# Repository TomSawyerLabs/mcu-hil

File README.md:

# mcu-hil

Hardware-in-the-loop boards for testing software against real microcontrollers.
A Raspberry Pi (Compute Module or standard Pi) powers, programs, clocks, resets and talks to
the microcontroller(s) on the board, so tests run against real silicon in a repeatable way.

AVRs come first (starting with the ATmega16U2 from v1). Other families (XMEGA, AVR32 UC3, and
more later) get their own boards built from the same base design.

## Variants

Each variant is a complete board with its MCU(s) on it. They share schematic sheets and one GPIO map.

- **CM4/CM5 carrier** (primary): same 55 × 40 mm outline as the Compute Module, so they stack.
  USB-C for power and rpiboot, Ethernet for network boot, microSD.
- **Pi HAT**: for 40-pin Raspberry Pi boards. Powered by the Pi; its USB-C is a data link back to
  the Pi through a short loopback cable.

Designed in KiCad. Every part has an LCSC part number and is chosen to be in stock, so boards can be
ordered fully assembled from JLCPCB.

## Status

v2 is being designed. See [plans/v2-design.md](plans/v2-design.md), the
[v1 design review](docs/v1-review.md), the [v2 requirements draft](docs/v2-requirements.md),
the [v2 pin map](docs/v2-pinmap.md), the [parts list](docs/v2-parts.md) and the
[schematic notes](docs/v2-schematic.md).

The KiCad 10 projects are in `hw/carrier/` and `hw/hat/`. Their schematics are generated from
[`tools/schgen/design.py`](tools/schgen/design.py) (`cd tools && python -m schgen`).

## v1 (AVR Test HAT)

This repo was `avr-test-hat`. The v1 design was an Altium project for a single Pi HAT with an
on-board ATmega16U2. Its files are no longer on `master` but are kept in history:

- Tag [`v1`](https://github.com/TomSawyerLabs/mcu-hil/tree/v1) (also branch
  [`v1-archive`](https://github.com/TomSawyerLabs/mcu-hil/tree/v1-archive)): the Altium project as it was.
- v1's simplified block diagram: [docs/v1-images/Circuits.drawio.svg](docs/v1-images/Circuits.drawio.svg).

v1 credits: [Raspberry Pi HAT Template](https://workspace.circuitmaker.com/Projects/Details/jonaslorander/Raspberry-Pi-HAT-Template)
by [Jonas Lorander](https://workspace.circuitmaker.com/User/Details/jonaslorander), and [SnapEDA](https://www.snapeda.com).

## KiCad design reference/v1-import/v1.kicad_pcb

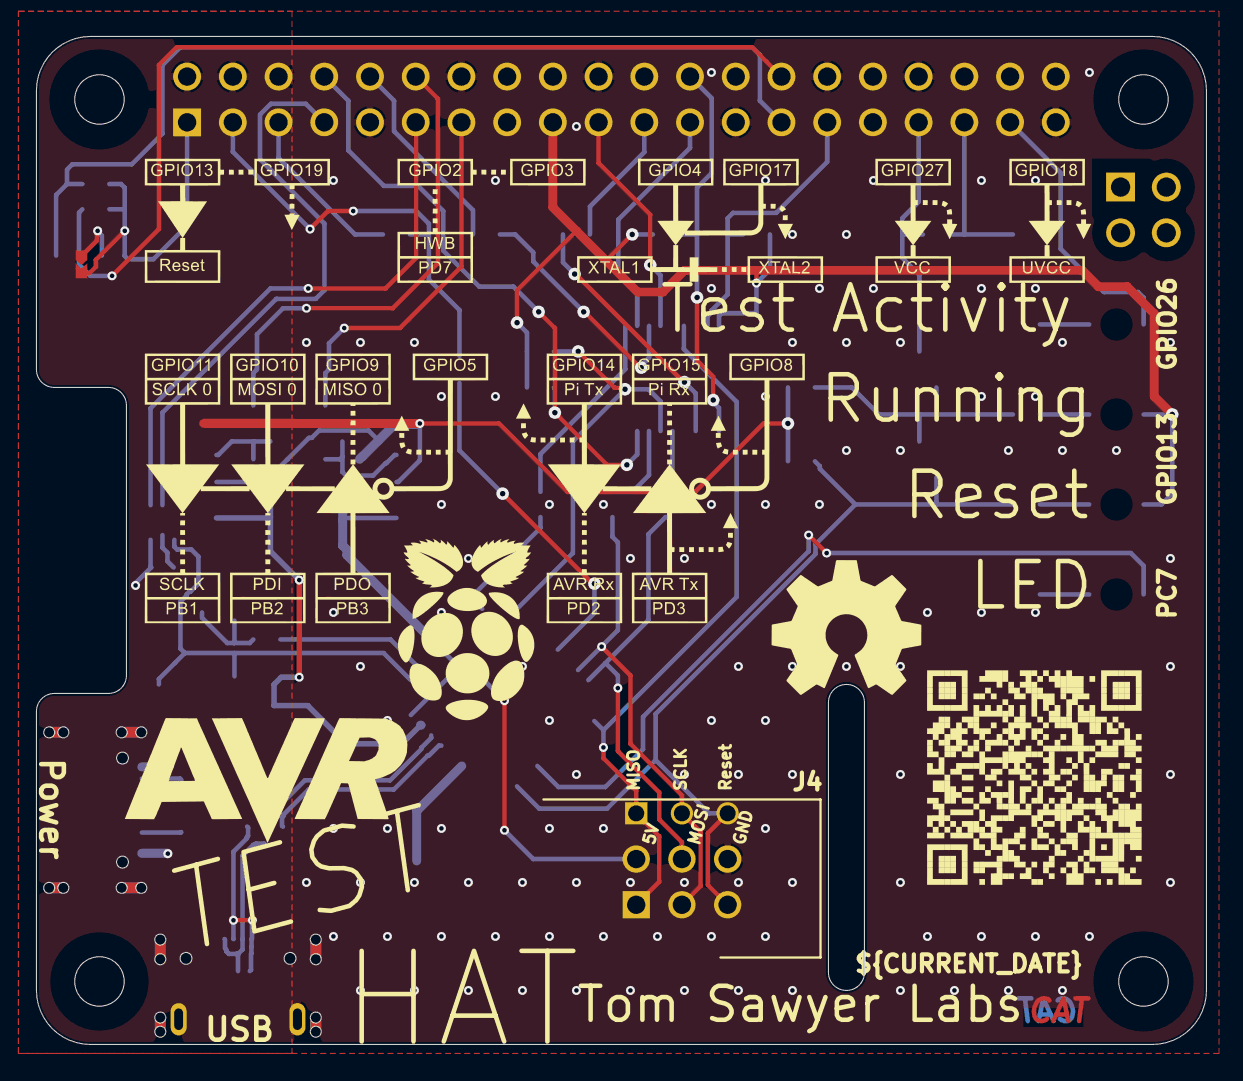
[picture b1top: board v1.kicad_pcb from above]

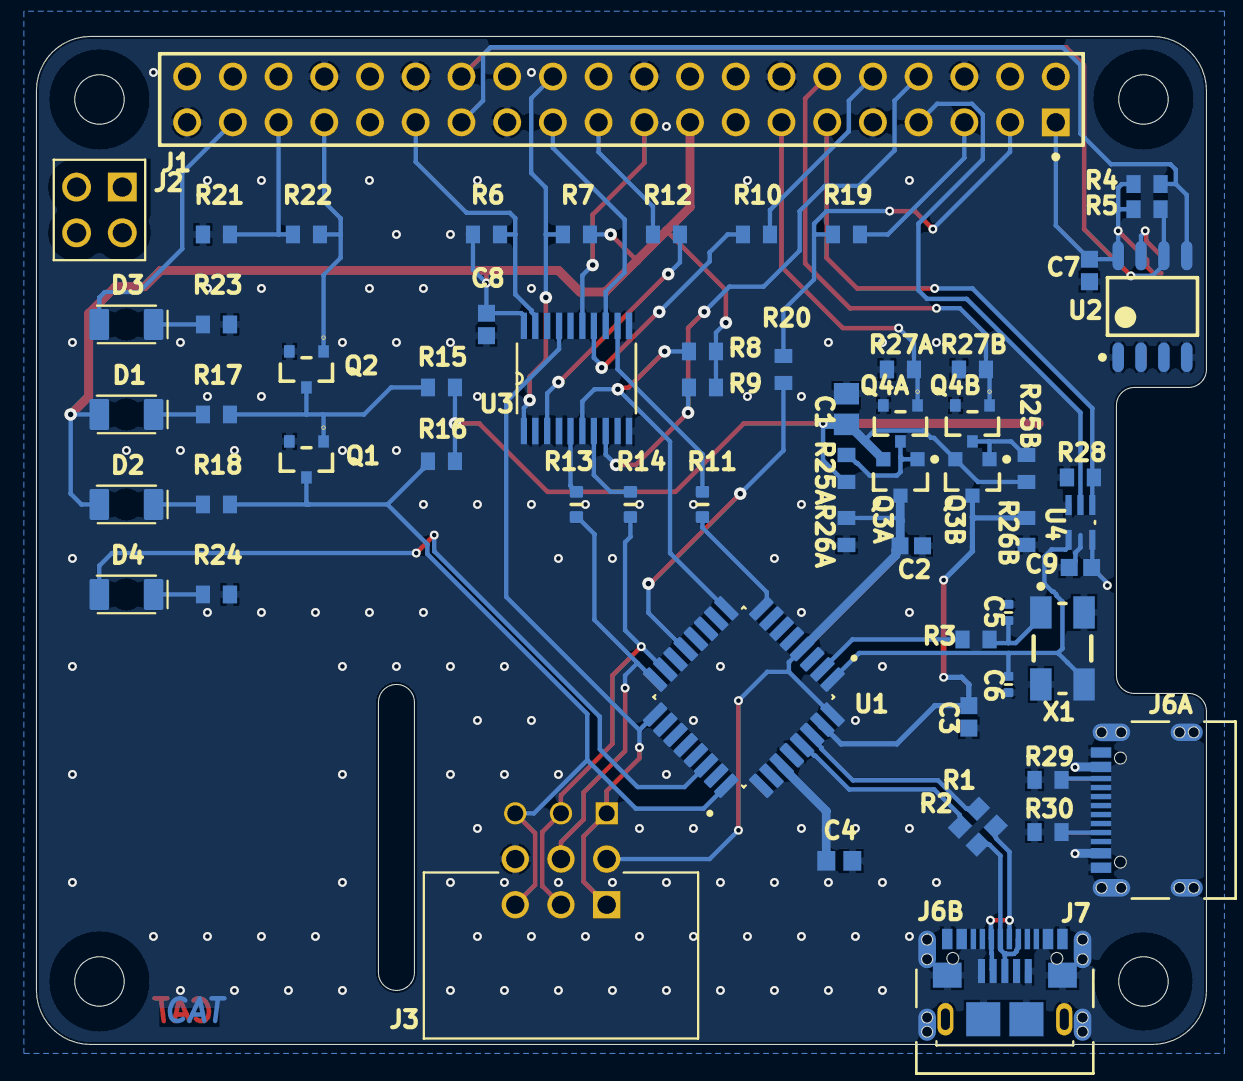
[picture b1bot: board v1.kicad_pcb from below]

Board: 2 copper layers, 65.0 x 56.0 mm, 65 parts (63 on the bottom side), 57 nets.

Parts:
C1: Capacitor 10 uF +/- 10% 16 V 0805; CAPC2013X135X45NL10T25
C2, C3, C7, C8, C9: Capacitor 100 nF +/-10% 50 V 0603; CAPC1608X90X40NL10T20
C4: Capacitor 1uF +/- 10% 16V 0603; CAPC1608X90X35ML15T15
C5, C6: Capacitor 12pF +/-10% 50V 0402; CAPC0402(1005)33_L
D1, D2, D3, D4: LTST-C230KFKT; LEDC3216X110
J1: Harwin M20-7832046; PCB-677180-1
J2: PPPC022LFBN-RC; SULLINS_PPPC022LFBN-RC
J3: 2-1761605-1; TE_2-1761605-1
J4: 30306-6002HB; 3M_30306-6002HB
J5: JUMPER
J6A, J6B: USB4105-GF-A; USB4105_GCT
J7: 10118193-0001LF; AMPHENOL_10118193-0001LF
Q1, Q2, Q4A, Q4B: 2N7002,215; NXP-SOT23-3_V
Q3A, Q3B: CJ2305; JSCJ-SOT23-3_V
R1, R2: Resistor 22R +/-1% 0603 100 mW; RESC1609X50X30ML08T20
R3, R4, R5, R6, R7, R8, R9, R10, R12, R15, R16, R17, R18, R19, R20, R21, R22, R23, R24, R25A, R25B, R26A, R26B, R27A, R27B, R28, R29, R30: Resistor 1k +/-1% 0603 100 mW; RESC1608X55X25ML10T15
R11, R13, R14: Resistor 120R +/-5 % 0603 0.1 W; RESC0603(1608)_L
U1: ATMEGA16U2-AU; QFP80P900X900X120-32N
U2: CAT24C32WI-GT3; ONSC-SOIC-8-751BD-01_M
U3: 74LVC244APW,118; SOP65P640X110-20N
U4: 74AHCT1G126SE-7; SOT65P210X110-5N
X1: ABM3B-16.000MHZ-B2-T; ABRA-ABM3B-4_V

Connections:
3V3: C7.2, C8.2, D1.A, D2.A, J1.1, J1.17, J5.2, R4.2, R5.2, R6.2, R7.2, R8.2, R9.2, U2.8, U3.20
5V: C1.1, C9.2, J1.2, J1.4, J6A.A4-B9, J6A.B4-A9, Q3A.2, Q3B.2, R15.2, R16.2, R25A.2, R25B.2, U4.5
AVR Activity: D4.A, U1.22
AVR Clock: C6.2, U1.1, U4.4, X1.3
AVR Rx: R11.2, U1.8
AVR Tx: R8.1, U1.9, U3.6
AVR USB Enable: J1.12, Q4B.1, R27B.2
AVR VCC Enable: J1.13, Q4A.1, R27A.2
A_N: R1.2, U1.30
A_P: R2.2, U1.29
Clock Override: J1.7, U4.2
Clock Override Enable: J1.11, R28.2, U4.1
DA_N: J6A.A7, J6A.B7
DA_P: J6A.A6, J6A.B6
DB_N: J6B.A7, J6B.B7, J7.2, R1.1
DB_P: J6B.A6, J6B.B6, J7.3, R2.1
Device_MISO: J3.1, J4.1, U1.17, U3.17
Device_MOSI: J3.4, J4.4, R13.2, U1.16
Device_SCLK: J3.3, J4.3, R14.2, U1.15
GND: C1.2, C2.1, C3.1, C4.2, C5.1, C6.1, C7.1, C8.1, C9.1, J1.6, J1.9, J1.14, J1.20, J1.25, J1.30, J1.34, J1.39, J3.6, J4.6, J6A.A1-B12, J6A.B1-A12, J6B.A1-B12, J6B.B1-A12, J7.5, J7.S1, J7.S2, J7.S3, J7.S4, J7.S5, J7.S6, Q1.2, Q2.2, Q4A.2, Q4B.2, R21.1, R23.1, R24.1, R26A.1, R26B.1, R27A.1, R27B.1, R28.1, R29.1, R30.1, U1.3, U1.28, U2.1, U2.2, U2.3, U2.4, U3.2, U3.4, U3.10, U3.11, U4.3, X1.2, X1.4
GPIO2: J1.3, R19.1, R20.2
GPIO3: J1.5, R19.2
GPIO5: J1.29, R6.1, U3.19
GPIO8: J1.24, R7.1, U3.1
GPIO9: J1.21, R12.1
GPIO10: J1.19, U3.15
GPIO11: J1.23, U3.13
GPIO13: J1.33, Q2.1, R22.1
GPIO14: J1.8, R9.1, U3.8
GPIO15: J1.10, R10.1
GPIO19: J1.35, R21.2, R22.2
GPIO26: D3.A, J1.37
HWB: R20.1, U1.13
ID_SC: J1.28, R5.1, U2.6
ID_SD: J1.27, R4.1, U2.5
NetC4_1: C4.1, U1.27
NetC5_2: C5.2, R3.1, X1.1
NetD1_C: D1.C, R17.2
NetD2_C: D2.C, R18.2
NetD3_C: D3.C, R23.2
NetD4_C: D4.C, R24.2
NetJ5_1: J5.1, U2.7
NetJ6A_A5: J6A.A5, R30.2
NetJ6A_B5: J6A.B5, R29.2
NetJ6B_A4-B9: J6B.A4-B9, J6B.B4-A9
NetQ1_1: Q1.1, Q2.3, R15.1, R17.1
NetQ3A_1: Q3A.1, Q4A.3, R25A.1
NetQ3B_1: Q3B.1, Q4B.3, R25B.1
NetR3_2: R3.2, U1.2
NetR10_2: R10.2, U3.14
NetR11_1: R11.1, U3.12
NetR12_2: R12.2, U3.3
NetR13_1: R13.1, U3.5
NetR14_1: R14.1, U3.7
Reset: J3.5, J4.5, Q1.3, R16.1, R18.1, U1.24
UVCC: C3.2, Q3B.3, R26B.2, U1.31
VCC: C2.2, J3.2, J4.2, Q3A.3, R26A.2, U1.4, U1.32

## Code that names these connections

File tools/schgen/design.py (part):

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    R(sh, "100k", "RST_GATE", "DUT_5V")
    NMOS(sh, "RST_GATE", "RESET_RELEASE")
    R(sh, "100k", "RESET_RELEASE", "GND")
    # HWB (PD7) assert.
    NMOS(sh, "DUT_PD7", "HWB_ASSERT")
    R(sh, "100k", "HWB_ASSERT", "GND")
    return sh
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def sheet_hv() -> Sheet:
    sh = Sheet("hv", "High-voltage programming (option HV)")
    sh.notes = [
        "12 V boost (MT3608, GPIO26) and a switch that puts it on RESET (GPIO25). Both default off.",
        "FB divider 100k/5.1k: 12.36 V nominal. The 1k series resistor drops about 0.25 V at the 250 uA RESET current,",
        "so RESET sees 11.9-12.4 V (spec 11.5-12.5 V).",
        "TCA6416A: VCCP on +5V (always up before +3V3, as TI recommends). ~RESET is pulled up to DUT_5V, so the",
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
# ------------------------------------------------------------------------------------------- carrier
CM_GPIO = {
    "GPIO2": "I2C_SDA", "GPIO3": "I2C_SCL", "GPIO4": "GPCLK0", "GPIO9": "ISP_MISO", "GPIO10": "ISP_MOSI",
    "GPIO11": "ISP_SCK", "GPIO12": "RESET_RELEASE", "GPIO13": "HWB_ASSERT", "GPIO14": "PI_TXD",
    "GPIO15": "PI_RXD", "GPIO16": "ISP_OE", "GPIO17": "UART_OE", "GPIO18": "CLK_OE", "GPIO19": "PWR_ALERT",
    "GPIO20": "USB_S0", "GPIO21": "USB_S1", "GPIO22": "DUT_PWR_EN", "GPIO24": "STATUS_LED",
    "GPIO25": "HV_APPLY", "GPIO26": "HV_BOOST_EN", "GPIO27": "SI_CLK_OE",
}


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    sh = Sheet("cm", "Compute Module 4/5 connectors", paper="A2")
    sh.notes = [
        "Hirose DF40C-100DS-0.4V(51), 1.5 mm stack. CM4 and CM5 share every pin used here.",
        "GPIO_VREF to +3V3 (3.3 V GPIO). ID_SD/ID_SC, GLOBAL_EN/PMIC_EN, EEPROM_nWP and the 1.8 V outputs are unused.",
        "CM5's USB-C CC pins (94/96) are left open: the carrier's own 5.1k Rd works for both CM4 and CM5",
        "(CM5 then runs without 5 A PD negotiation).",
    ]
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        "HAT+ rules: ID_SD/ID_SC carry only the EEPROM and 3.9k pull-ups to 3.3 V. EEPROM WP has a 1k pull-up;",
        "bridge JP1 (or drive the test point low) to write it. The HAT never powers the Pi.",
        "USB-C here is a data port only: a short cable back to one of the Pi's USB host ports. Its VBUS is not used.",
        "GPIO2/3 already have ~2k pull-ups on the Pi. STANDBY (5 V up, 3.3 V down) is safe: every enable defaults off.",
    ]
    sh.add(Part("Connector_Generic:Conn_02x20_Odd_Even", "Pi 40-pin", {str(k): v for k, v in HAT_HEADER.items()},
                footprint="Connector_PinSocket_2.54mm:PinSocket_2x20_P2.54mm_Vertical", lcsc="C5124634",
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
